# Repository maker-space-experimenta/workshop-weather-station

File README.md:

# workshop-weather-station

developed for a workshop at maker space exeprimenta heilbronn.

It's a simple weather station made from

- 2 Arduino Nano
- 2 NRF24
- 1 OLED Display (128x64)
- 1 DHT22

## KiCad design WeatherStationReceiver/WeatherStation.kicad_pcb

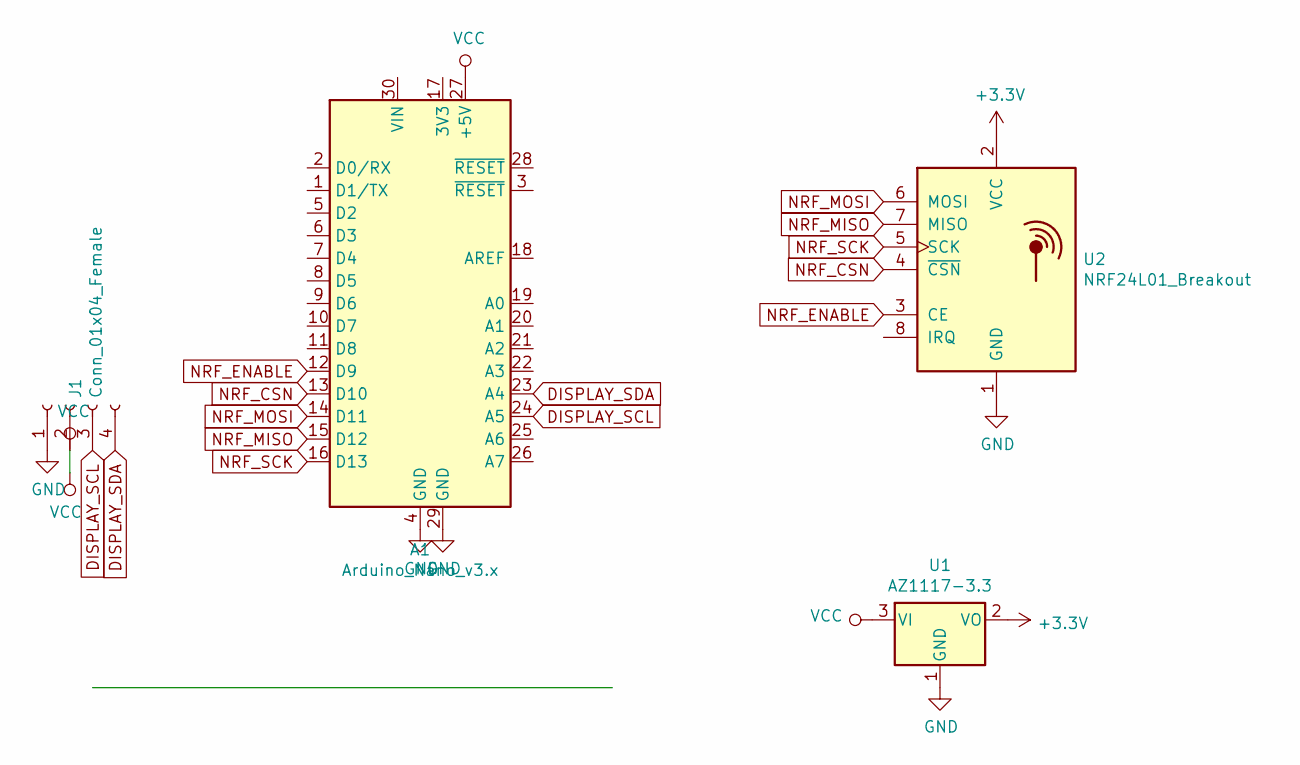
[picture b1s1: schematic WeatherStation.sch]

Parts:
A1: Arduino_Nano_v3.x; Arduino_Nano
J1: Conn_01x04_Female; PinSocket_1x04_P2.54mm_Vertical
U1: AZ1117-3.3; TO-220-3_Horizontal_TabDown
U2: NRF24L01_Breakout; nRF24L01_Breakout

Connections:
+3V3: U1.2 (VO), U2.2 (VCC)
DISPLAY_SCL: A1.24 (A5), J1.3
DISPLAY_SDA: A1.23 (A4), J1.4
GND: A1.4 (GND), A1.29 (GND), J1.1, U1.1 (GND), U2.1 (GND)
NRF_CSN: A1.13 (D10), U2.4 (~CSN)
NRF_ENABLE: A1.12 (D9), U2.3 (CE)
NRF_MISO: A1.15 (D12), U2.7 (MISO)
NRF_MOSI: A1.14 (D11), U2.6 (MOSI)
NRF_SCK: A1.16 (D13), U2.5 (SCK)
VCC: A1.27 (+5V), J1.2, U1.3 (VI)

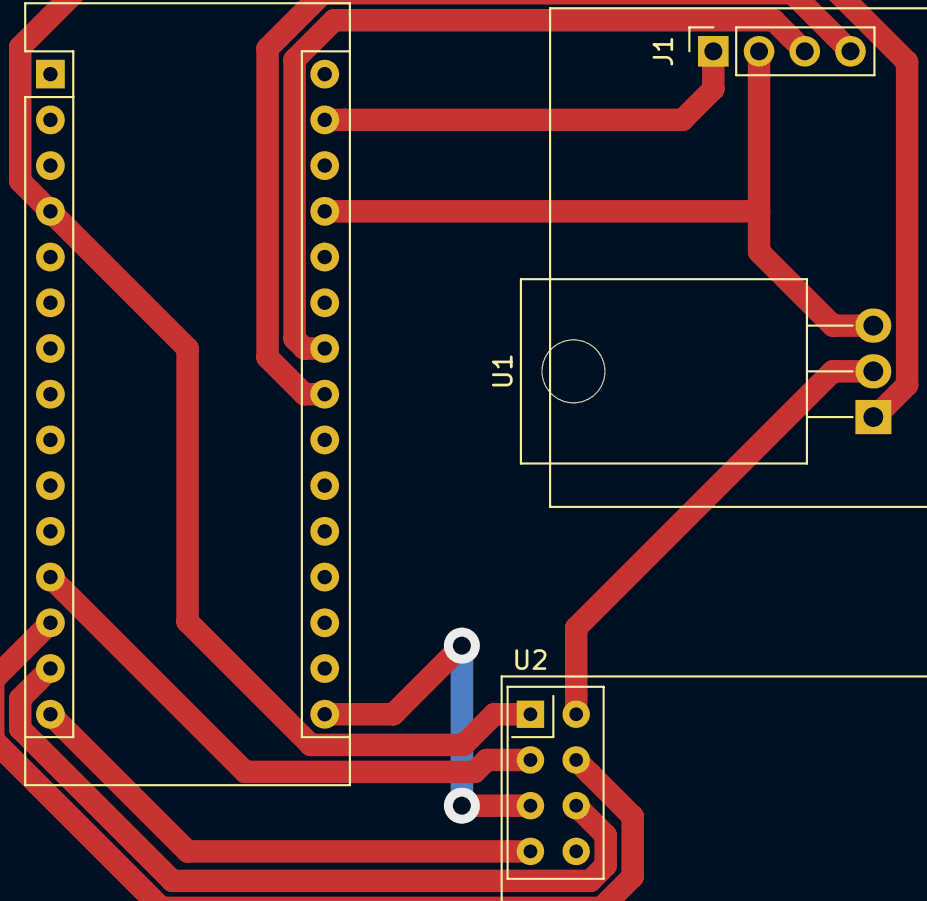
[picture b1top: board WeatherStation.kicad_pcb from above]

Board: 2 copper layers, 4 parts (0 on the bottom side), 10 nets.

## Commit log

2020-02-09 millable pcb for receiver, boot sequence in arduino with spash screen
2020-02-10 working code with deep sleep, sending, receiving data, UI finished
2020-02-10 finished pcb for order
